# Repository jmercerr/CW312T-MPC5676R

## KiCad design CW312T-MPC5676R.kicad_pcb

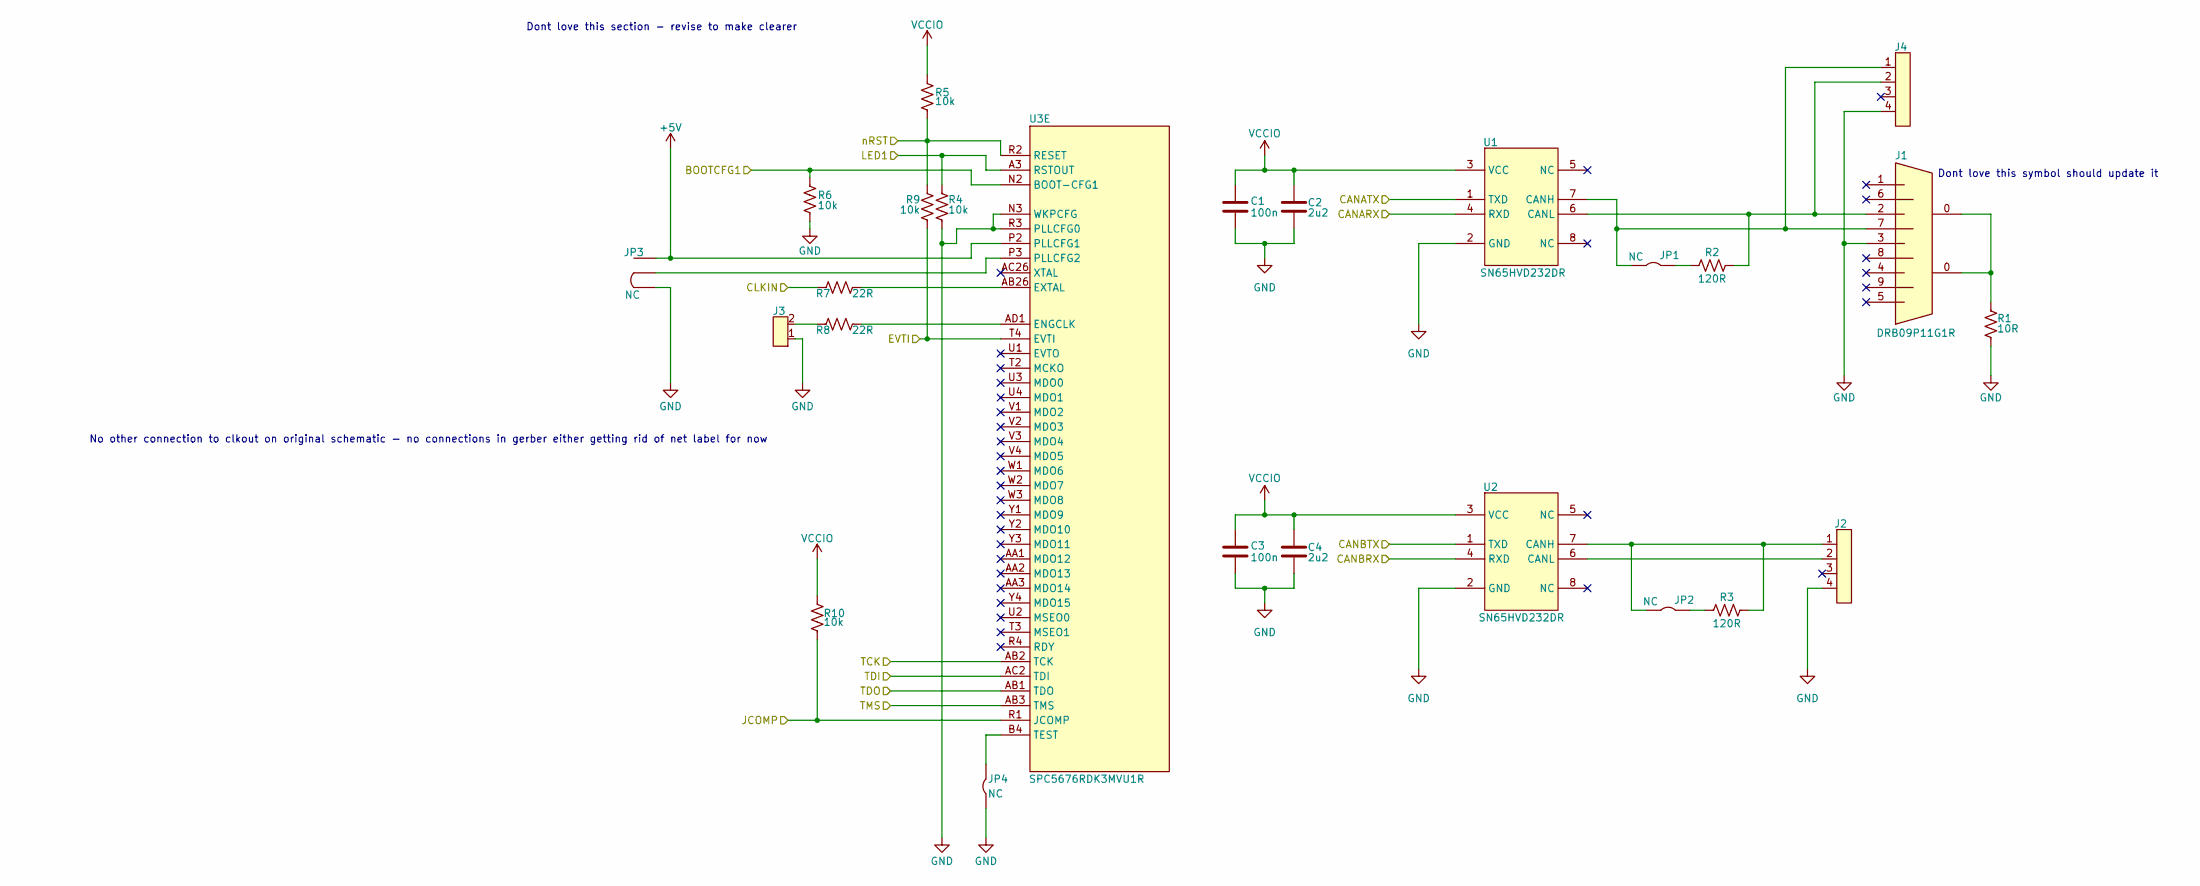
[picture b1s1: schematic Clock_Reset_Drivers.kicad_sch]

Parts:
C1, C3: CAP_100n_16V_0402; C_0402_1005Metric; Manufacturer Part Number CC0402KRX7R7BB104
C2, C4: CAP_2u2_10V_0603; C_0603_1608Metric; Manufacturer Part Number CC0603KPX7R6BB225
J1: DRB09P11G1R; DSUB-9_Male_Horizontal_P2.77x2.84mm_EdgePinOffset9.90mm_Hou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; Manufacturer Part Number 618009231421
J2, J4: HDR_4_2.54; PinHeader_1x04_P1.00mm_Vertical; Manufacturer Part Number HMTSW-104-23-L-S-237
J3: 2Pin_Header_2.54; PinHeader_2x01_P2.54mm_Vertical; Manufacturer Part Number M20-9990246
JP1, JP2, JP4: SolderJumper-2_P1.3mm_Bridged2Bar_Pad1.0x1.5mm
JP3: SolderJumper-3_P1.3mm_Bridged2Bar12_Pad1.0x1.5mm
R1: RES_10R_0603; R_0603_1608Metric; Manufacturer Part Number RC0603FR-0710RL
R2, R3: RES_120R_0603; R_0603_1608Metric; Manufacturer Part Number RC0603FR-07120RL
R4, R5, R6, R9, R10: RES_10k_0603; R_0603_1608Metric; Manufacturer Part Number RC0603FR-0710KL
R7, R8: RES_22R_0603; R_0603_1608Metric; Manufacturer Part Number RC0603FR-0722RL
U1, U2: SN65HVD232DR; SOIC-8_3.9x4.9mm_P1.27mm; Manufacturer Part Number SN65HVD232DR
U3: SPC5676RDK3MVU1R; BGA416C100P26X26_2700X2700X255N; Manufacturer Part Number SPC5676RDK3MVU1R

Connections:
+5V: JP3.3, U3.P2 (PLLCFG1); also elsewhere on the board
/CPU IO Bank 2/CANARX: U1.4 (RXD); also elsewhere on the board
/CPU IO Bank 2/CANATX: U1.1 (TXD); also elsewhere on the board
/CPU IO Bank 2/CANBRX: U2.4 (RXD); also elsewhere on the board
/CPU IO Bank 2/CANBTX: U2.1 (TXD); also elsewhere on the board
/CW312T-Connector/BOOTCFG1: R6.2, U3.N2 (BOOT-CFG1); also elsewhere on the board
/CW312T-Connector/CLKIN: R7.1; also elsewhere on the board
/CW312T-Connector/EVTI: R9.1, U3.T4 (EVTI); also elsewhere on the board
/CW312T-Connector/JCOMP: R10.1, U3.R1 (JCOMP); also elsewhere on the board
/CW312T-Connector/LED1: R4.2, U3.A3 (RSTOUT); also elsewhere on the board
/CW312T-Connector/TCK: U3.AB2 (TCK); also elsewhere on the board
/CW312T-Connector/TDI: U3.AC2 (TDI); also elsewhere on the board
/CW312T-Connector/TDO: U3.AB1 (TDO); also elsewhere on the board
/CW312T-Connector/TMS: U3.AB3 (TMS); also elsewhere on the board
/CW312T-Connector/nRST: R5.1, R9.2, U3.R2 (RESET); also elsewhere on the board
GND: C1.1, C2.1, C3.1, C4.1, J1.3, J2.4, J3.1, J4.4, JP3.1, JP4.2, R1.1, R4.1, R6.1, U1.2 (GND), U2.2 (GND), U3.N3 (WKPCFG), U3.R3 (PLLCFG0); also elsewhere on the board
unnamed: J1.0, R1.2
unnamed: J3.2, R8.1
unnamed: J1.2, J4.2, R2.2, U1.6 (CANL)
unnamed: J2.2, U2.6 (CANL)
unnamed: R8.2, U3.AD1 (ENGCLK)
unnamed: R7.2, U3.AB26 (EXTAL)
unnamed: JP3.2, U3.P3 (PLLCFG2)
unnamed: JP4.1, U3.B4 (TEST)
VCCIO: C1.2, C2.2, C3.2, C4.2, R5.2, R10.2, U1.3 (VCC), U2.3 (VCC); also elsewhere on the board

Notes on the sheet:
Dont love this symbol should update it
No other connection to clkout on original schematic - no connections in gerber either getting rid of net label for now
Dont love this section - revise to make clearer

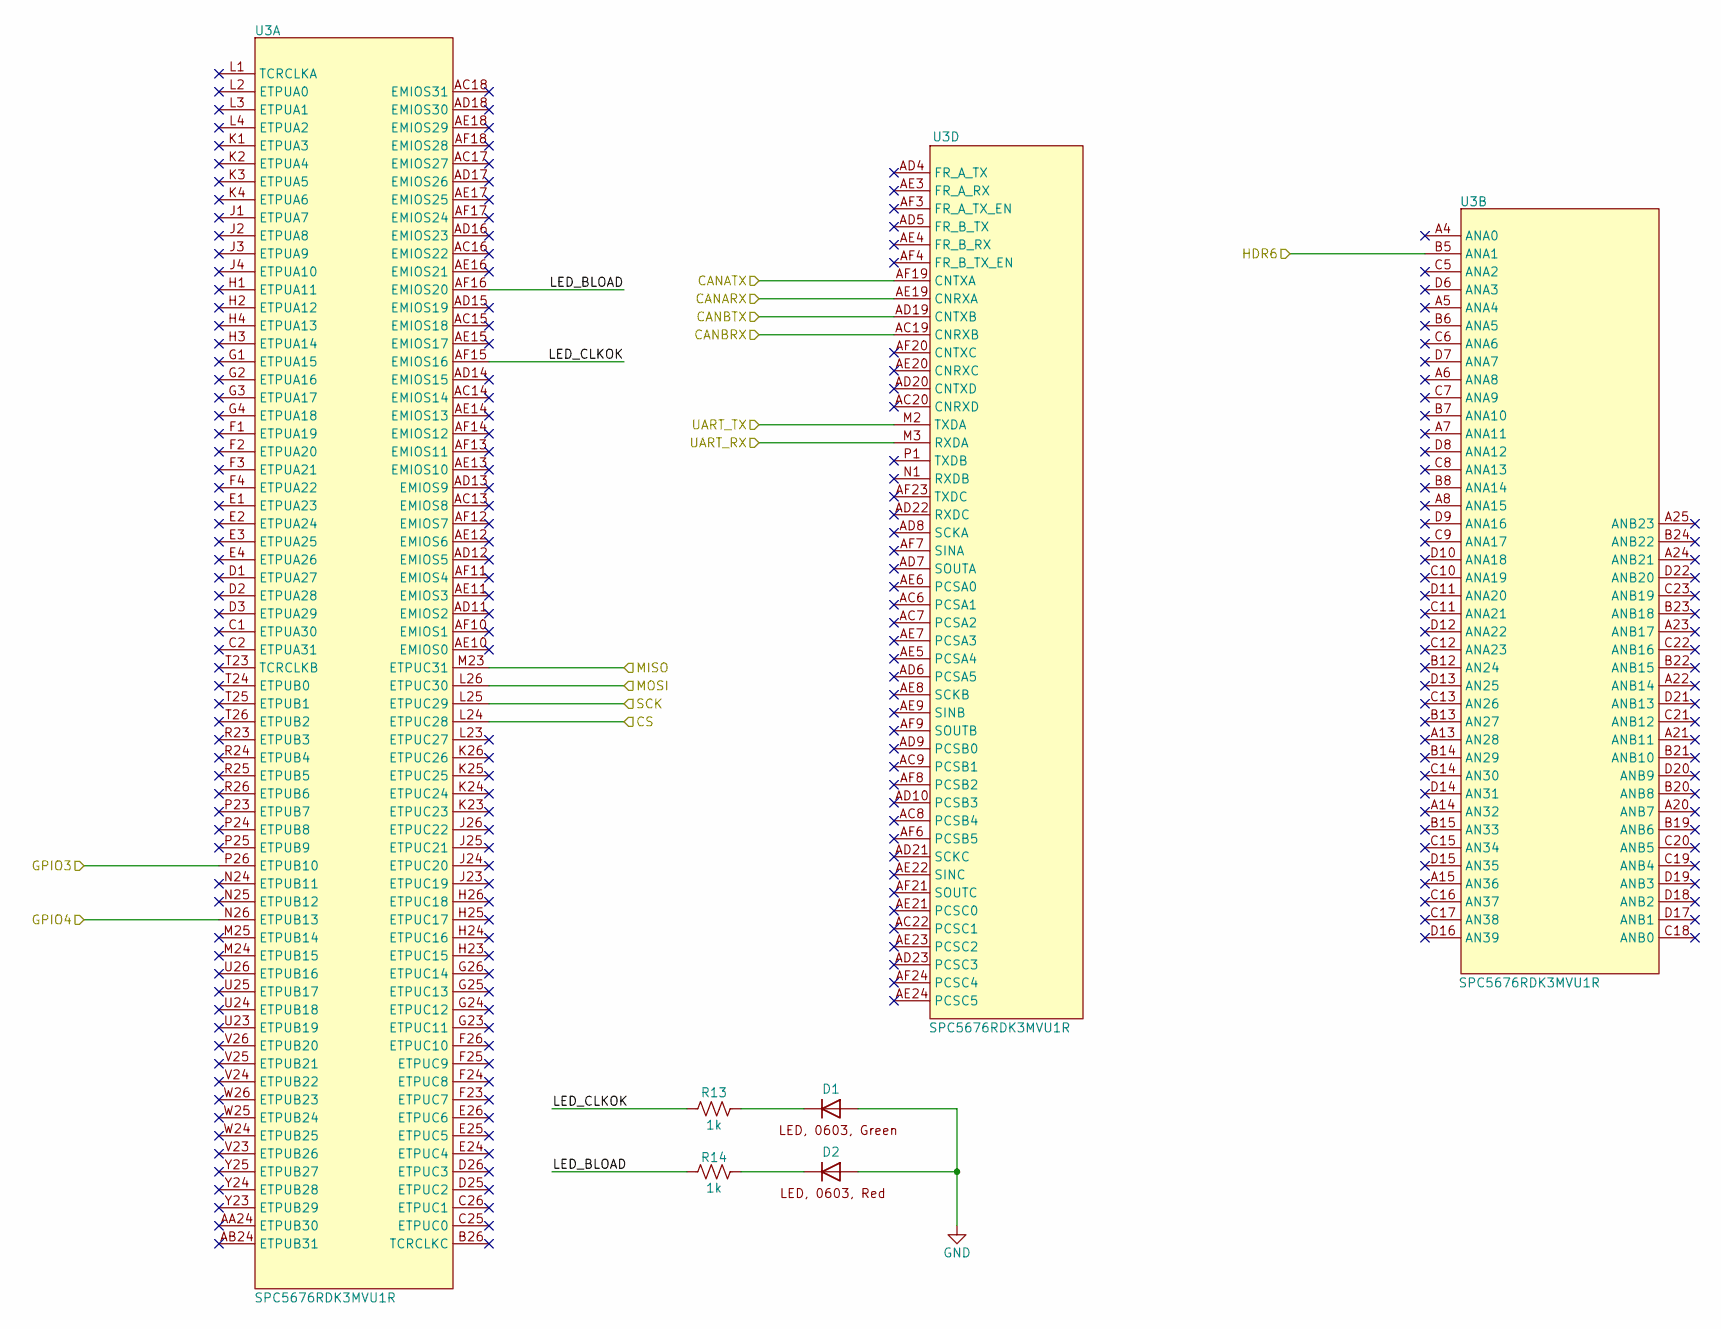
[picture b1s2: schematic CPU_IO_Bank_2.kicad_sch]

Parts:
D1, D2: APT1608SRCPRV; LED_0603_1608Metric; Manufacturer Part Number APT1608SRCPRV
R13, R14: RES_1k_0603; R_0603_1608Metric; Manufacturer Part Number RC0603FR-071KL
U3: SPC5676RDK3MVU1R; BGA416C100P26X26_2700X2700X255N; Manufacturer Part Number SPC5676RDK3MVU1R

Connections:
/CPU IO Bank 2/CANARX: U3.AE19 (CNRXA); also elsewhere on the board
/CPU IO Bank 2/CANATX: U3.AF19 (CNTXA); also elsewhere on the board
/CPU IO Bank 2/CANBRX: U3.AC19 (CNRXB); also elsewhere on the board
/CPU IO Bank 2/CANBTX: U3.AD19 (CNTXB); also elsewhere on the board
/CPU IO Bank 2/CS: U3.L24 (ETPUC28); also elsewhere on the board
/CPU IO Bank 2/GPIO3: U3.P26 (ETPUB10); also elsewhere on the board
/CPU IO Bank 2/GPIO4: U3.N26 (ETPUB13); also elsewhere on the board
/CPU IO Bank 2/HDR6: U3.B5 (ANA1); also elsewhere on the board
/CPU IO Bank 2/LED_BLOAD: R14.1, U3.AF16 (EMIOS20)
/CPU IO Bank 2/LED_CLKOK: R13.1, U3.AF15 (EMIOS16)
/CPU IO Bank 2/MISO: U3.M23 (ETPUC31); also elsewhere on the board
/CPU IO Bank 2/MOSI: U3.L26 (ETPUC30); also elsewhere on the board
/CPU IO Bank 2/SCK: U3.L25 (ETPUC29); also elsewhere on the board
/CPU IO Bank 2/UART_RX: U3.M3 (RXDA); also elsewhere on the board
/CPU IO Bank 2/UART_TX: U3.M2 (TXDA); also elsewhere on the board
GND: D1.2, D2.2; also elsewhere on the board
unnamed: D1.1, R13.2
unnamed: D2.1, R14.2

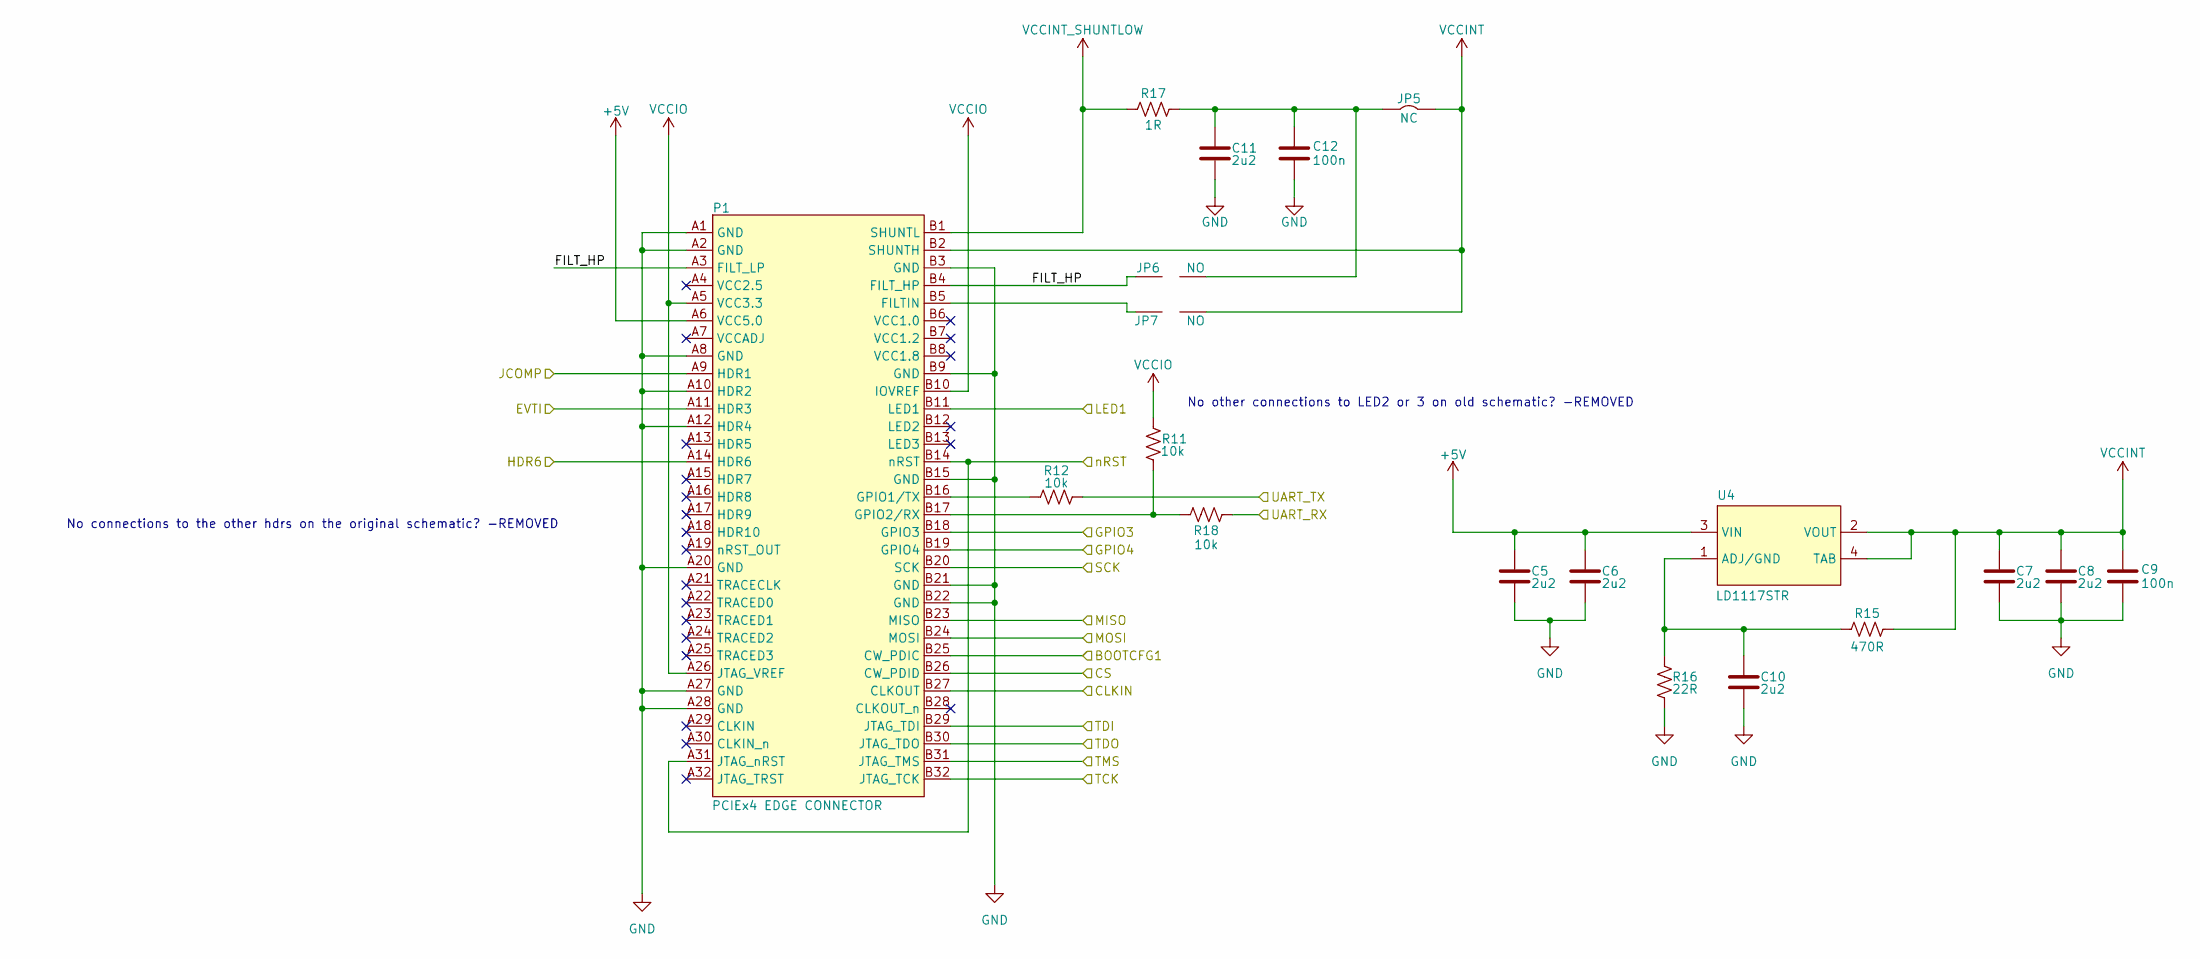
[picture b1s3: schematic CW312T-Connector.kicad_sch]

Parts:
C5, C6, C7, C8, C10, C11: CAP_2u2_10V_0603; C_0603_1608Metric; Manufacturer Part Number CC0603KPX7R6BB225
C9, C12: CAP_100n_16V_0402; C_0402_1005Metric; Manufacturer Part Number CC0402KRX7R7BB104
JP5: SolderJumper-2_P1.3mm_Bridged2Bar_Pad1.0x1.5mm
JP6, JP7: SolderJumper-2_P1.3mm_Open_Pad1.0x1.5mm
P1: PCIEx4 EDGE CONNECTOR; CW312_Template
R11, R12, R18: RES_10k_0603; R_0603_1608Metric; Manufacturer Part Number RC0603FR-0710KL
R15: RES_470R_0603; R_0603_1608Metric; Manufacturer Part Number RC0603FR-13470RL
R16: RES_22R_0603; R_0603_1608Metric; Manufacturer Part Number RC0603FR-0722RL
R17: RES_1R_0805; R_0805_2012Metric; Manufacturer Part Number RC0805FR-071RL
U4: LD1117STR; SOT-223; Manufacturer Part Number LD1117STR

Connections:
+5V: C5.2, C6.2, P1.A6 (VCC5.0), U4.3 (VIN); also elsewhere on the board
/CPU IO Bank 2/CS: P1.B26 (CW_PDID); also elsewhere on the board
/CPU IO Bank 2/GPIO3: P1.B19 (GPIO4); also elsewhere on the board
/CPU IO Bank 2/GPIO4: P1.B18 (GPIO3); also elsewhere on the board
/CPU IO Bank 2/HDR6: P1.A14 (HDR6); also elsewhere on the board
/CPU IO Bank 2/MISO: P1.B23 (MISO); also elsewhere on the board
/CPU IO Bank 2/MOSI: P1.B24 (MOSI); also elsewhere on the board
/CPU IO Bank 2/SCK: P1.B20 (SCK); also elsewhere on the board
/CPU IO Bank 2/UART_RX: R18.2; also elsewhere on the board
/CPU IO Bank 2/UART_TX: R12.2; also elsewhere on the board
/CW312T-Connector/BOOTCFG1: P1.B25 (CW_PDIC); also elsewhere on the board
/CW312T-Connector/CLKIN: P1.B27 (CLKOUT); also elsewhere on the board
/CW312T-Connector/EVTI: P1.A11 (HDR3); also elsewhere on the board
/CW312T-Connector/FILT_HP: JP6.2, P1.A3 (FILT_LP), P1.B4 (FILT_HP)
/CW312T-Connector/JCOMP: P1.A9 (HDR1); also elsewhere on the board
/CW312T-Connector/LED1: P1.B11 (LED1); also elsewhere on the board
/CW312T-Connector/TCK: P1.B32 (JTAG_TCK); also elsewhere on the board
/CW312T-Connector/TDI: P1.B29 (JTAG_TDI); also elsewhere on the board
/CW312T-Connector/TDO: P1.B30 (JTAG_TDO); also elsewhere on the board
/CW312T-Connector/TMS: P1.B31 (JTAG_TMS); also elsewhere on the board
/CW312T-Connector/nRST: P1.A31 (JTAG_nRST), P1.B14 (nRST); also elsewhere on the board
GND: C5.1, C6.1, C7.1, C8.1, C9.1, C10.1, C11.1, C12.1, P1.A1 (GND), P1.A2 (GND), P1.A8 (GND), P1.A10 (HDR2), P1.A12 (HDR4), P1.A20 (GND), P1.A27 (GND), P1.A28 (GND), P1.B3 (GND), P1.B9 (GND), P1.B15 (GND), P1.B21 (GND), P1.B22 (GND), R16.1; also elsewhere on the board
unnamed: C11.2, C12.2, JP5.2, JP6.1, R17.2
unnamed: JP7.2, P1.B5 (FILTIN)
unnamed: P1.B16 (GPIO1/TX), R12.1
unnamed: P1.B17 (GPIO2/RX), R11.1, R18.1
unnamed: C10.2, R15.1, R16.2, U4.1 (ADJ/GND)
VCCINT: C7.2, C8.2, C9.2, JP5.1, JP7.1, P1.B2 (SHUNTH), R15.2, U4.2 (VOUT), U4.4 (TAB)
VCCINT_SHUNTLOW: P1.B1 (SHUNTL), R17.1; also elsewhere on the board
VCCIO: P1.A5 (VCC3.3), P1.A26 (JTAG_VREF), P1.B10 (IOVREF), R11.2; also elsewhere on the board

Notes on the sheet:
No connections to the other hdrs on the original schematic? -REMOVED
No other connections to LED2 or 3 on old schematic? -REMOVED

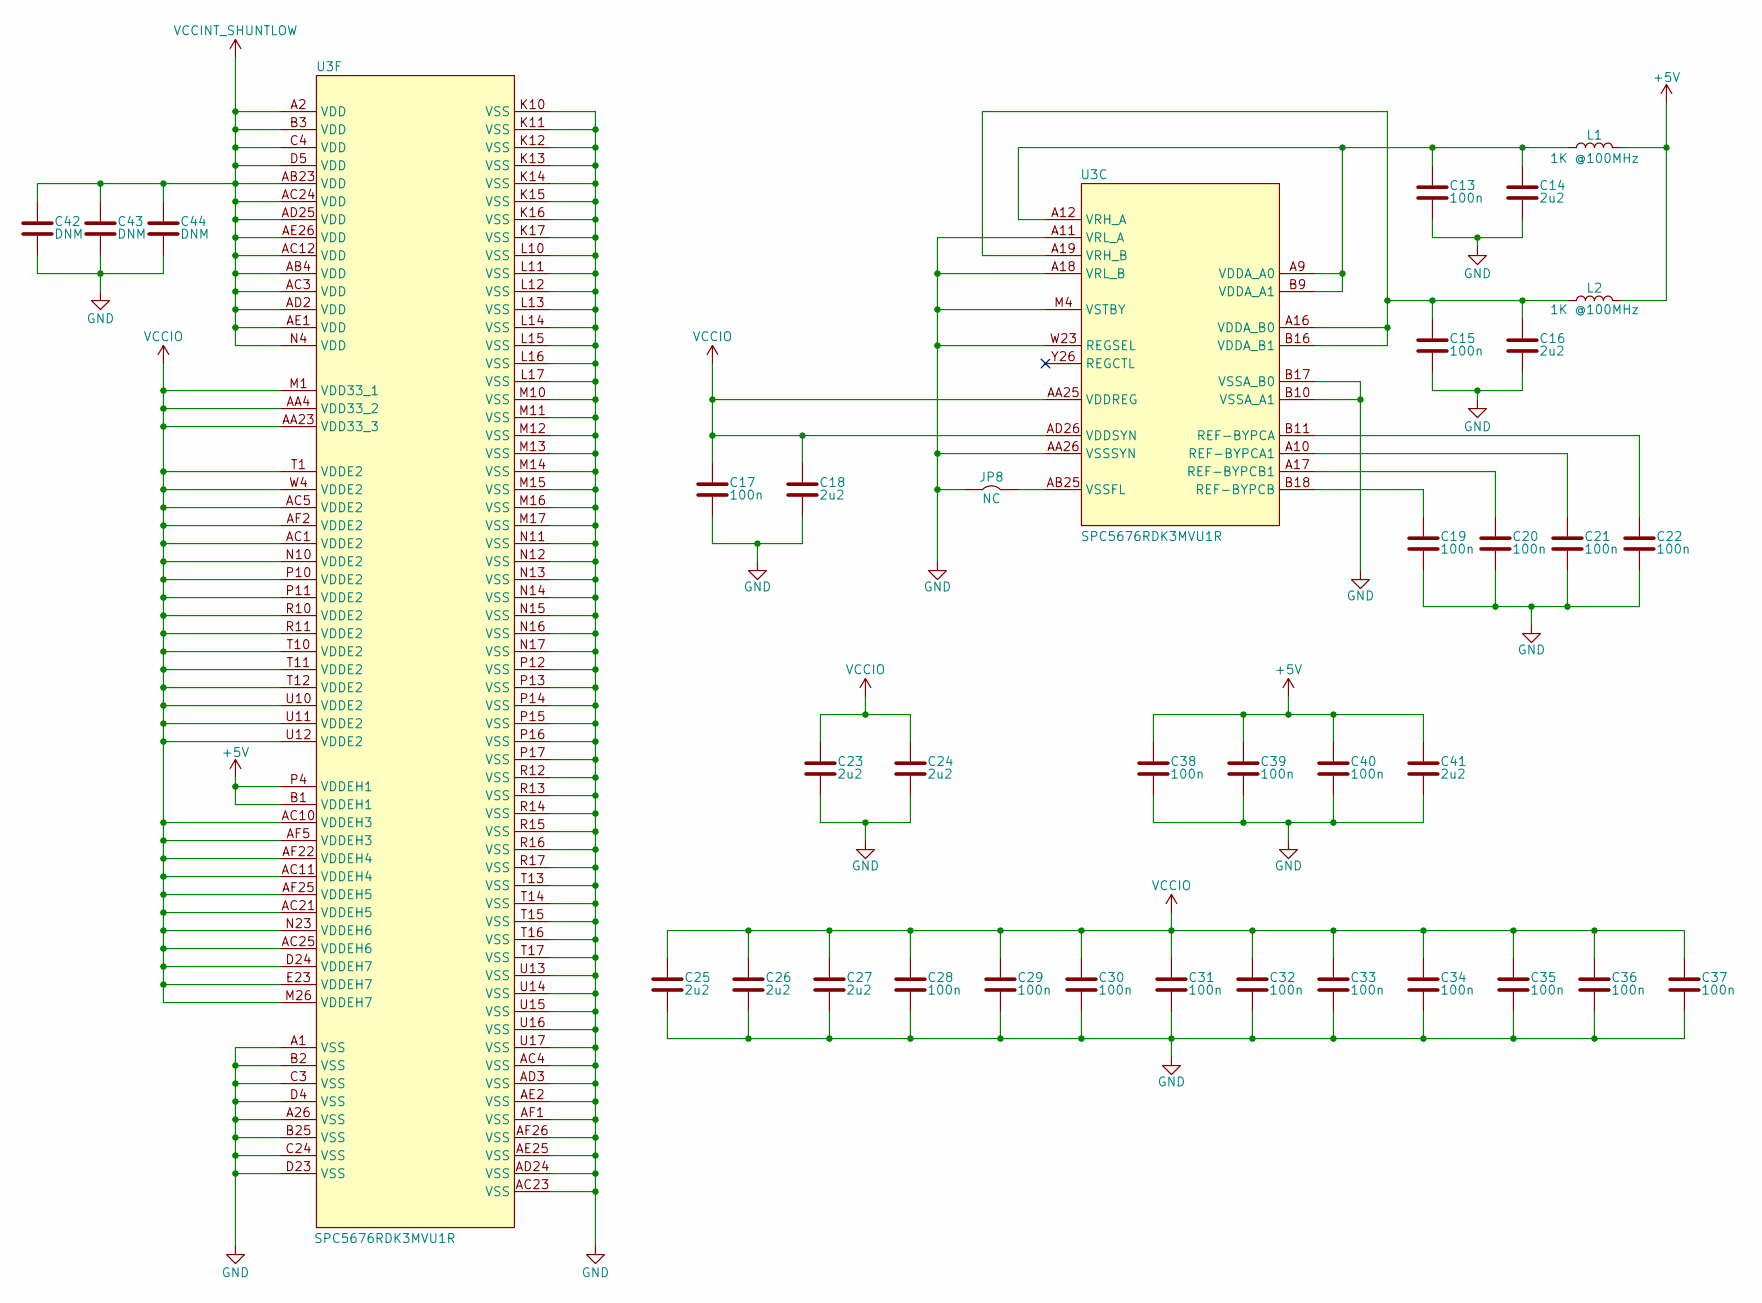
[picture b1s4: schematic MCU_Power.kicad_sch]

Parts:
C13, C15, C17, C19, C20, C21, C22, C28, C29, C30, C31, C32, C33, C34, C35, C36, C37, C38, C39, C40: CAP_100n_16V_0402; C_0402_1005Metric; Manufacturer Part Number CC0402KRX7R7BB104
C14, C16, C18, C23, C24, C25, C26, C27, C41: CAP_2u2_10V_0603; C_0603_1608Metric; Manufacturer Part Number CC0603KPX7R6BB225
C42, C43, C44: CAP_DNM_0402; C_0402_1005Metric
JP8: SolderJumper-2_P1.3mm_Bridged2Bar_Pad1.0x1.5mm
L1, L2: IND_1K_0603; L_0603_1608Metric; Manufacturer Part Number FBMH1608HM102-T
U3: SPC5676RDK3MVU1R; BGA416C100P26X26_2700X2700X255N; Manufacturer Part Number SPC5676RDK3MVU1R

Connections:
+5V: C38.2, C39.2, C40.2, C41.2, L1.2, L2.2, U3.B1 (VDDEH1), U3.P4 (VDDEH1); also elsewhere on the board
GND: C13.1, C14.1, C15.1, C16.1, C17.1, C18.1, C19.1, C20.1, C21.1, C22.1, C23.1, C24.1, C25.1, C26.1, C27.1, C28.1, C29.1, C30.1, C31.1, C32.1, C33.1, C34.1, C35.1, C36.1, C37.1, C38.1, C39.1, C40.1, C41.1, C42.1, C43.1, C44.1, JP8.2, U3.A1 (VSS), U3.A11 (VRL_A), U3.A18 (VRL_B), U3.A26 (VSS), U3.AA26 (VSSSYN), U3.AC4 (VSS), U3.AC23 (VSS), U3.AD3 (VSS), U3.AD24 (VSS), U3.AE2 (VSS), U3.AE25 (VSS), U3.AF1 (VSS), U3.AF26 (VSS), U3.B2 (VSS), U3.B10 (VSSA_A1), U3.B17 (VSSA_B0), U3.B25 (VSS), U3.C3 (VSS), U3.C24 (VSS), U3.D4 (VSS), U3.D23 (VSS), U3.K10 (VSS), U3.K11 (VSS), U3.K12 (VSS), U3.K13 (VSS), U3.K14 (VSS), U3.K15 (VSS), U3.K16 (VSS), U3.K17 (VSS), U3.L10 (VSS), U3.L11 (VSS), U3.L12 (VSS), U3.L13 (VSS), U3.L14 (VSS), U3.L15 (VSS), U3.L16 (VSS), U3.L17 (VSS), U3.M4 (VSTBY), U3.M10 (VSS), U3.M11 (VSS), U3.M12 (VSS), U3.M13 (VSS), U3.M14 (VSS), U3.M15 (VSS), U3.M16 (VSS), U3.M17 (VSS), U3.N11 (VSS), U3.N12 (VSS), U3.N13 (VSS), U3.N14 (VSS), U3.N15 (VSS), U3.N16 (VSS), U3.N17 (VSS), U3.P12 (VSS), U3.P13 (VSS), U3.P14 (VSS), U3.P15 (VSS), U3.P16 (VSS), U3.P17 (VSS), U3.R12 (VSS), U3.R13 (VSS), U3.R14 (VSS), U3.R15 (VSS), U3.R16 (VSS), U3.R17 (VSS), U3.T13 (VSS), U3.T14 (VSS), U3.T15 (VSS), U3.T16 (VSS), U3.T17 (VSS), U3.U13 (VSS), U3.U14 (VSS), U3.U15 (VSS), U3.U16 (VSS), U3.U17 (VSS), U3.W23 (REGSEL); also elsewhere on the board
unnamed: C21.2, U3.A10 (REF-BYPCA1)
unnamed: C22.2, U3.B11 (REF-BYPCA)
unnamed: C20.2, U3.A17 (REF-BYPCB1)
unnamed: C19.2, U3.B18 (REF-BYPCB)
unnamed: C13.2, C14.2, L1.1, U3.A9 (VDDA_A0), U3.A12 (VRH_A), U3.B9 (VDDA_A1)
unnamed: C15.2, C16.2, L2.1, U3.A16 (VDDA_B0), U3.A19 (VRH_B), U3.B16 (VDDA_B1)
unnamed: JP8.1, U3.AB25 (VSSFL)
VCCINT_SHUNTLOW: C42.2, C43.2, C44.2, U3.A2 (VDD), U3.AB4 (VDD), U3.AB23 (VDD), U3.AC3 (VDD), U3.AC12 (VDD), U3.AC24 (VDD), U3.AD2 (VDD), U3.AD25 (VDD), U3.AE1 (VDD), U3.AE26 (VDD), U3.B3 (VDD), U3.C4 (VDD), U3.D5 (VDD), U3.N4 (VDD); also elsewhere on the board
VCCIO: C17.2, C18.2, C23.2, C24.2, C25.2, C26.2, C27.2, C28.2, C29.2, C30.2, C31.2, C32.2, C33.2, C34.2, C35.2, C36.2, C37.2, U3.AA4 (VDD33_2), U3.AA23 (VDD33_3), U3.AA25 (VDDREG), U3.AC1 (VDDE2), U3.AC5 (VDDE2), U3.AC10 (VDDEH3), U3.AC11 (VDDEH4), U3.AC21 (VDDEH5), U3.AC25 (VDDEH6), U3.AD26 (VDDSYN), U3.AF2 (VDDE2), U3.AF5 (VDDEH3), U3.AF22 (VDDEH4), U3.AF25 (VDDEH5), U3.D24 (VDDEH7), U3.E23 (VDDEH7), U3.M1 (VDD33_1), U3.M26 (VDDEH7), U3.N10 (VDDE2), U3.N23 (VDDEH6), U3.P10 (VDDE2), U3.P11 (VDDE2), U3.R10 (VDDE2), U3.R11 (VDDE2), U3.T1 (VDDE2), U3.T10 (VDDE2), U3.T11 (VDDE2), U3.T12 (VDDE2), U3.U10 (VDDE2), U3.U11 (VDDE2), U3.U12 (VDDE2), U3.W4 (VDDE2); also elsewhere on the board

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
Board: 2 copper layers, 83 parts (0 on the bottom side), 57 nets, no tracks yet.

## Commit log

2024-12-18 draft updated, schematic draft done, pcb issues with size of board and fitting all parts on
2024-12-19 updated schematic after library re-organization
